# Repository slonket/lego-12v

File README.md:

# Lego 12V

### An assortment of projects to supplement the Lego 12V "Gray" era trains.

## Project Structure

This is the high-level directory for projects within this repository. All projects follow the same general file structure, though some hierarchical items may be missing if the project does not require them (e.g. `/firmware/` for a project without an MCU):
- `/hardware/` - PCBA project.
    - `/panel/` - panelized PCBA project for manufacturing.
    - `/production_files/` - production files for the PCBA project (including BOM and POS files).
- `/firmware/` - embedded firmware for MCU(s) contained within PCBA project.
- `/mechanical/` - 3D models (`.step`) for the physical item(s).
    - `/outlines/` - 2D profiles (`.dxf`) related to PCB design, etched parts, etc.

### Miscellaneous Items

Some items do not pertain to a higher level project and can be found within the `/_misc/` directory. These are individually documented with a brief description in `/_misc/README.md`.

## PCBA

### PCBA Production

The PCBA projects are designed with production using JLCPCB in mind. As such, the exported gerbers, placement, and BOM files are all formatted for JLCPCB and their parts library. Detailed instructions for ordering parts can be found within each project.

### KiCAD Libraries

All PCBA projects within this repository use the Slonket KiCAD libraries. If you wish to modify a PCBA project, you will need to download the [Slonket Footprints](https://github.com/slonket/slonket-footprints) repository and add the contained libraries as "Global" within KiCAD. You do not need to use KiCAD when ordering items within this repository - as detailed above, each project already contains the necessary production files for ordering.

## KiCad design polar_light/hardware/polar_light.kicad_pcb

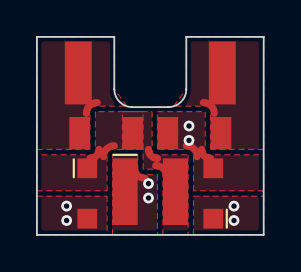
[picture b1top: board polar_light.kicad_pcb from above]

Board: 2 copper layers, 12.6 x 11.0 mm, 7 parts (0 on the bottom side), 5 nets.

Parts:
D1, D3: SM4007PL; D_SOD-123F
D2: GREEN; D_LED_4040
J1: PIN_A; J_Pad_1_Lego
J2: PIN_B; J_Pad_1_Lego
R1, R2: 270; R_1206

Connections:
/PIN_A: J1.1, R1.1
/PIN_B: J2.1, R2.2
unnamed: D1.2 (A), D3.1 (K)
unnamed: D1.1 (K), D2.2 (A), R1.2
unnamed: D2.1 (K), D3.2 (A), R2.1

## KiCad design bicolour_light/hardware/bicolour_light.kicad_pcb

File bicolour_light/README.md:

# Bicolour Light

### A bicolour LED version of the 12V 2x2 light brick.

The brick contains two red/yellow bicolour LEDs which change colour with input polarity. This brick is intended for use in locomotives/rolling stock to produce a headlight/tail-light changeover with direction.

### Features

- Identical formfactor to the original 2x2 12V light brick (08010bc01).
- Version with 3-hole socket.
- Colour change red-yellow with input polarity.
- Improved brightness over original, particularly in the lower voltage range.

### Specifications

| PARAMETER | VALUE | UNIT | CONDITION |
| --------- | ----- | ---- | --------- |
| V_max | 12 | V | |
| I_max | 39 | mA | V = 12V |
| W_red | 625 | nm | Individual; IF = 20mA |
| W_yel | 585 | nm | Individual; IF = 20mA |

## Usage Information

The position of the LEDs is ideal for use with light prism assemblies (4170/4171). Each LED is positioned directly behind its respective light prism, allowing for the majority of light to be guided to the exterior stud. The combination of LED positioning and efficiency results in an overall brighter effect than the original bulbs. The chosen colours of red/yellow mimic the original colours of the bulb bricks when combined with red/yellow studs. As such, it is recommended to use clear studs instead of the original tinted studs on the light prisms for the best effect.

**NOTE:** As a consequence of using forward-facing LEDs, light is almost entirely directed forward. This makes the bricks ineffective for downward lighting, such as within train interiors or affixed as station lampposts.

## Ordering Information

Parts can be ordered through JLCPCB/JLC3DP using the included production files. You can produce your own production files for a different service using the KiCAD source projects.

**NOTE:** You are ordering these items at **your own risk**! While care is taken to ensure projects are complete and functional, mistakes and errors are always possible. The creators of this project do not hold any liability or responsibility for items you have had produced from this repository.

## Ordering PCBA

The production files are for a panel containing 4 individual PCBs. As such, the ordered quantity will be `4 * n_panel`. If you order 5 PCBs/Panels, for example, you will receive 20 individual PCBs to produce 20 bicolour light bricks.

- Upload `/hardware/production_files/bicolour_light_X4.zip` to the JLCPCB ordering page with these **changed** options:
    - **PCB (Panel) Quantity** - Your choice! (default 5).
    - **Delivery Format** - Panel By Customer
    - **Panel Format** - Column: **2** - Row: **2**
    - **PCB Thickness** - 1.0mm
    - (optional) **Surface Finish** - LeadFree HASL
    - **Mark on PCB** - Order Number (Specify Position)
- Enable "PCB Assembly"
    - **PCBA Quantity** - Your choice! (default 5)
    - **Tooling Holes** - Added by Customer
- Check options with the image below; proceed with "Next"
- Check the displayed PCB and proceed with "Next"
- Upload the following files and select the following option:
    - **Add BOM File:** - `/hardware/production_files/bicolour_light_BOM.xlsx`
    - **Add CPL File:** - `/hardware/production_files/bicolour_light_X4_POS.xlsx`
    - **File provided as:** - Complete File
- Proceed with "Process BOM & CPL"
- Check the supplied inventory (see PCBA Issues) and proceed with "Confirm"
- Check placement (see PCBA Issues) and add to cart - Done!

**NOTE:** When paying for your PCBA order, you should have access to a $9 discount coupon - this can offset the cost of PCBA for a small order.

### PCBA Issues

The LED used is an uncommon part and will likely have no active inventory in the PCBA system. You can pre-order the LED through JLCPCB's part system; this will guarantee inventory for when you place your PCBA order. The LCSC part number is [C7545694](https://jlcpcb.com/partdetail/XINGLIGHT-XLC4040SURUYC/C7545694).

The placement origin of the LED differs within the PCBA service than the KiCAD footprint. This will result in the LEDs placement being slightly forward. Please correct this in the placement view, or select "Confirm Parts Placement" when ordering. The correct placement is 0.25mm inset from the board edge (you can approximate this in the placement view).

## Ordering 3D Parts

3D models are supplied in `.step` format for portability. JLC3DP accepts `.step` files for 3D printing, though many slicers for home printing do not. If you would like to print these files yourself, you will need to re-export them to `.stl` using a CAD package of your choice. Follow the below procedure for ordering parts using JLC3DP:

- Upload the following files to the JLC3DP ordering page and select their respective options:
    - `/mechanical/bicolour_light_housing.step`
        - **3D Technology** - SLA (Resin)
        - **Material** - Gray Resin
        - **Surface Finish** - Yes - Sanding
        - **QTY** - Your choice! Match the number of _individual_ PCBs ordered
        - **Product Desc** - Enclosure -> Plastic Enclosure
    - `/mechanical/bicolour_light_lens.step`
        - **3D Technology** - SLA (Resin)
        - **Material** - 8001 Resin
        - **Color** - Translucent
        - **Surface Finish** - No
        - **QTY** - Your choice! Match the number of _individual_ PCBs ordered
        - **Product Desc** - Enclosure -> Plastic Enclosure
- Add to cart - Done!

**NOTE:** The lens pieces made in 8001 Resin are considered "small parts". You will receive an error if you attempt to order them with a surface finish.

### 3D Part Issues

There is a possibility that you will be contacted regarding manufacturability after placing an order. This is typically due to the "12V" text legibility on the rear of the housing. The precision of this text is not crucial; you can respond to the inquiry stating that you accept the possibility of defects. Even when not explicitly highlighted by JLC, any resin printed part can possess defects such as scratches, warping/deformation, variance in finished size, etc. Two orders of the same parts will result in slight differences. The models have been designed with sufficient tolerance, though you may still need to perform some finishing for a proper assembled fit. This variance also affects the clutch power of the bricks when binding with Lego original parts - some will be a little tight, others a little loose.

## Assembly Instructions

These instructions assume you have ordered parts using the instructions above. The required processing and finishing will differ if you have printed the 3D parts yourself.

1. Depanelize the PCBs by breaking along the mousebites. Break the edge rails first, then break the PCBs from the inner frame.
2. Deburr the broken mousebites by running a sharp blade along their edges. Be careful not to cut the PCB itself. Ensure you do this on a suitable cutting surface where you can safely contain and dispose of the PCB fragments.
3. Check the underside of the 3D printed lens - you may need to sand the antistud for appropriate binding force. There may be residual artifacts from printing on the antistud side - gently sand these away.
4. Place a PCB into the lens with the LEDs occupying the corrugated cavity. The unpopulated side should be facing up.
5. Insert the lens-PCB assembly into the housing. You will need to use a small amount of force to overcome the three housing clips. Once located, ensure the three clips are securely fastened over the lens.

**NOTE:** For any sanding of 3D printed parts, it is best to use a fine-grit emery board. Sand gently and check fitment often so as not to remove excess material. Clean sanded parts with a toothbrush to remove dust residue.

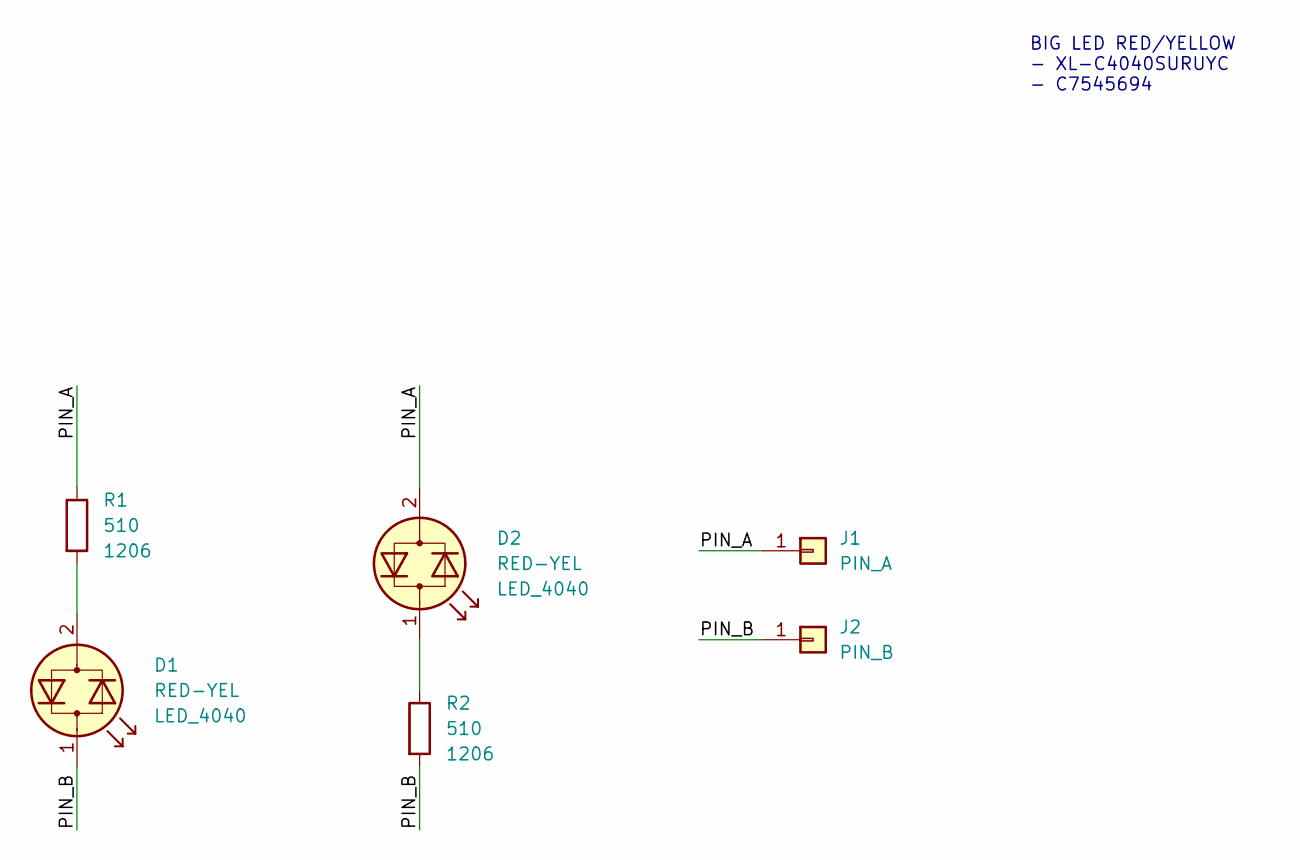
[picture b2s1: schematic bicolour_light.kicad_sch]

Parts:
D1, D2: RED-YEL; D_LED_4040; LCSC C7545694
J1: PIN_A; J_Pad_1_Lego
J2: PIN_B; J_Pad_1_Lego
R1, R2: 510; R_1206; LCSC C25386

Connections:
/PIN_A: D2.2 (AK), J1.1, R1.1
/PIN_B: D1.1 (KA), J2.1, R2.2
unnamed: D1.2 (AK), R1.2
unnamed: D2.1 (KA), R2.1

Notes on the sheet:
BIG LED RED/YELLOW - XL-C4040SURUYC - C7545694

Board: 2 copper layers, 6 parts (0 on the bottom side), 4 nets, no tracks yet.

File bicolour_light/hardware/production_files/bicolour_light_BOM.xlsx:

Comment | Designator | Footprint | LCSC
RED-YEL | D1,D2 | D_LED_4040 | C7545694
510 | R1,R2 | 1206 | C25386

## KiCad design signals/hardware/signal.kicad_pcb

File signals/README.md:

# Signals (Incomplete WIP)

### Re-imagined 12V signal bricks in the style of German "Hp" light signals

The majority of 12V gray-era sets are inspired by the Deutsche Bundesbahn (DB); even the turnouts feature a "lantern" brick akin to those on German turnouts. The 12V signal brick (70022), however, does not hold a connection to a real German counterpart. This project reimagines the Lego signal head as two different German Hp signals ("home" and "entry") while maintaining the original's blocky charm.

**NOTE:** "TLG signal", "Lego signal", "12V Lego signal head" and any similar combination all refer to the brick (70022). The mast and other components are currently not the subject of this project.

### Design Considerations

The foundation of this project is the question "what if TLG _did_ model their signal after a German original?". As such, an intersection of design considerations appears from the constraints of TLG's signal head, and the shape of a German Hp signal. These are the constraints I've distilled that satisfy a union of both:

- Must be a similar size to the signal brick.
- Must be dimensioned using the 1.6mm "Lego unit".
- Must use 5mm THT LEDs.
- Signal cowls should inherit the dimensions of the signal brick.
- Should connect to the mast brick (4168) similarly to the signal brick.

### Features

- Functions identically to the original signal.
- Size of two stacked 2x4 plates.
- Two different versions:
    - "Home" displaying Hp0 (red) and Hp1 (green).
    - "Entry" displaying Hp0 (red) and Hp2 (yellow + green).
- Jumper studs for centered mounting on mast.
- BYO LEDs! Your choice of brightness and colours.

### Specifications

| PARAMETER | VALUE | UNIT | CONDITION |
| --------- | ----- | ---- | --------- |
| V_max | 12 | V | |
| I_max | 39 | mA | V = 12V |

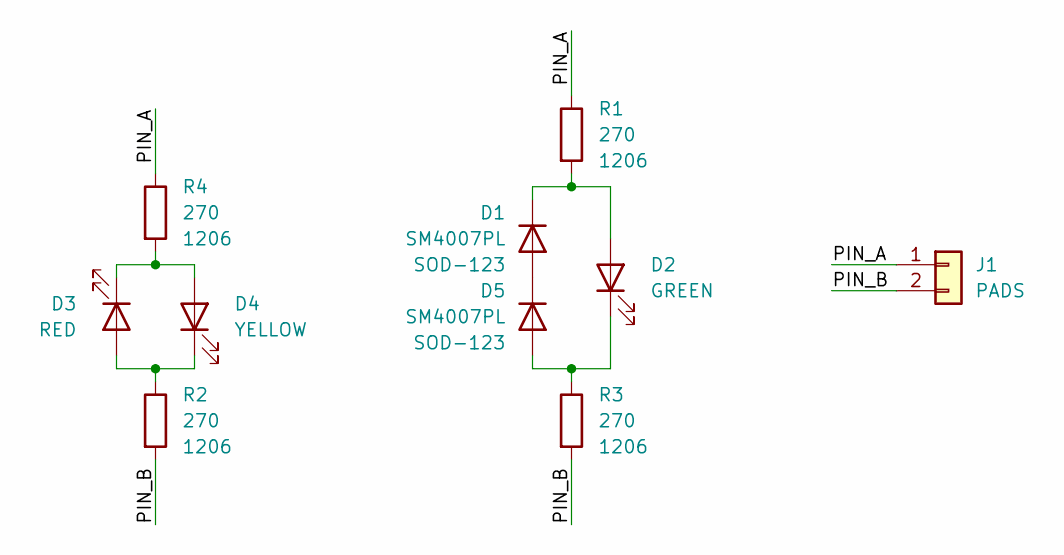
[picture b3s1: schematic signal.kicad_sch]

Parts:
D1, D5: SM4007PL; D_SOD-123F; LCSC C64898
D2: GREEN; D_LED_5mm
D3: RED; D_LED_5mm
D4: YELLOW; D_LED_5mm
J1: PADS; J_Pad_2_T15
R1, R2, R3, R4: 270; R_1206; LCSC C25366

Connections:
/PIN_A: J1.1, R1.1, R4.1
/PIN_B: J1.2, R2.2, R3.2
unnamed: D1.2 (A), D5.1 (K)
unnamed: D1.1 (K), D2.2 (A), R1.2
unnamed: D2.1 (K), D5.2 (A), R3.1
unnamed: D3.2 (A), D4.1 (K), R2.1
unnamed: D3.1 (K), D4.2 (A), R4.2

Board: 2 copper layers, 10 parts (1 on the bottom side), 7 nets, no tracks yet.

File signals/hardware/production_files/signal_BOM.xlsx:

Comment | Designator | Footprint | LCSC
SM4007PL | D1,D5 | SOD-123F | C64898
270 | R1,R2,R3,R4 | 1206 | C25366

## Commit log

2025-09-01 Initial grandfathering of existing project items
2025-09-01 Added basic readme for control box
2025-09-03 Added polar light (single yellow LED)
2025-12-19 Added bufferless beam
